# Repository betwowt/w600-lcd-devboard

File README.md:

# W600 LCD DevBoard

**用两块钱的 W600 模组和一块 ILI9341 240×320 屏，做出一块能点屏、能触摸、能读卡、能存图的开源板。**
硬件（KiCad / Gerber / BOM / 3D）、固件、构建脚本和实测记录都在这个仓库里。

## 为什么做这块板

W600 是 WinnerMicro 2019 年的模组，逛某宝时两元一片，卖家说兼容 ESP8266。
买回来实测发现：模块自带的 AT 固件是裁剪版，没有 HTTP / MQTT 专用 AT、
server 模式和 OTA，多轮 socket 开关后状态机还会残留（详见
[`docs/W600-AT-baseline.md`](docs/W600-AT-baseline.md)）。

既然 AT 不够用，就基于 W600 SDK 自己写固件。于是有了这块板：把点屏要用的
FPC、触摸、外部 Flash、TF 卡，以及按键、RGB 灯和 USB-C 串口都做上，
顺手把 LCD / Flash / SD 三设备共享 SPI 的坑也踩完了。

## 特性

- **显示**：ILI9341 240×320 SPI，20 MHz 硬件 SPI 刷屏，1bpp 图像快速展开
- **触摸**：FT6236 / CST816 自动探测，I2C 轮询，支持画板演示
- **存储**：板载 W25Q64（8 MB）+ TF 卡，FAT16/32 文件流
- **开机 logo**：TF 卡 `/logo.bin` 同步到 Flash，之后从 Flash 流式刷屏
- **Bad Apple**：TF 卡实时播放 1bpp 帧流，RLE 压缩，240×180 实测 18 fps
- **交互**：4 个用户按键 + 共阳 RGB 灯，全部挂在 XL9555 上
- **自检**：一块固件检查 LCD、Flash、TF 卡和 Wi-Fi，失败时串口打印具体阶段
- **共享总线**：LCD / Flash / SD 共用 SPI，单总线任务 + CS 互锁，不会互相踩
- **全开源**：原理图、PCB、Gerber、BOM、LCSC 库、3D 模型和固件源码都在仓库里

## 硬件

| 项目 | 规格 |
| --- | --- |
| MCU | WinnerMicro W600（TW-03），Cortex-M3 @ 80 MHz，2.4 GHz 802.11 b/g/n |
| 存储 | 1 MB Flash / 288 KB SRAM |
| 模组封装 | ESP-12F 兼容封装 |
| 屏幕 | ILI9341 240×320，16Pin 0.5 mm FPC，SPI，无 MISO |
| 触摸 | FT6236 / CST816，I2C，TP_INT 可选 |
| 外部 Flash | W25Q64，8 MB，SPI NOR |
| 存储卡 | TF 卡槽，SPI 模式，FAT16/32 |
| IO 扩展 | XL9555，16 位 I2C GPIO，地址 `0x24` |
| USB | USB-C 供电 + CH340N USB-UART |
| 电源 | AMS1117-3.3，USB-C 5 V 输入 |
| 按键 | 4 个用户键（KEY0–KEY3）+ 1 个复位键 |
| 指示灯 | XL-1615RGBC-RF 共阳 RGB，低有效 |
| PCB | 2 层，1.6 mm，约 45.8 × 34.6 mm |

```mermaid
flowchart LR
  PC[USB-C 5V] --> LDO[AMS1117-3.3]
  USB[USB-C D+/D-] --> CH[CH340N]
  CH -->|UART| W[W600]
  W -->|SPI PA01/PB18/PB17| BUS{共享 SPI 总线}
  BUS --> LCD[ILI9341 240x320]
  BUS --> FL[W25Q64 8MB]
  BUS --> TF[TF 卡]
  W -->|I2C PB09/PB12| X[XL9555]
  X --> LCD
  X --> KEY[4 按键]
  X --> RGB[RGB LED]
  W -->|I2C PB13/PB14| TP[FT6236/CST816]
```

### 引脚分配

| 信号 | W600 / 扩展 | 说明 |
| --- | --- | --- |
| SPI_CLK | PA01 | LCD / Flash / SD 共用，AF option 3 |
| SPI_MOSI | PB18 | 共用，AF option 3 |
| SPI_MISO | PB17 | Flash / SD 共用；LCD 不接 MISO |
| LCD_CS | PB11 | GPIO 片选，低有效 |
| LCD_DC | XL9555 P0_3 | 命令/数据 |
| LCD_RST | XL9555 P0_0 | 低有效 |
| LCD_PWR | XL9555 P0_2 | 高有效（面板使能/背光电源） |
| FLASH_CS | PB15 | W25Q64 片选，低有效 |
| SD_CS | PB16 | TF 卡片选，低有效 |
| XL9555_SCL | PB09 | 软件 I2C（该脚无硬件 I2C 复用） |
| XL9555_SDA | PB12 | 软件 I2C，4.7 kΩ 上拉 |
| XL9555_INT | PB08 | 本仓库未使用 |
| TOUCH_SCL | PB13 | 触摸 I2C，4.7 kΩ 上拉 |
| TOUCH_SDA | PB14 | 触摸 I2C，4.7 kΩ 上拉 |
| TP_RST | XL9555 P0_1 | 触摸复位，低有效 |
| TP_INT | PB10 | 触摸中断，本例程轮询 |
| KEY0–KEY3 | XL9555 P0_4–P0_7 | 10 kΩ 上拉，按下为低 |
| LED_R/G/B | XL9555 P1_0–P1_2 | 共阳 +3.3 V，低有效 |

注意：`PB11/PB12` 被 LCD_CS 和 XL9555 占用，SDK 默认 UART1 不能同时使用。

### 关键器件

| 器件 | 型号 | 封装 / LCSC |
| --- | --- | --- |
| 主控模组 | W600 / TW-03 | ESP-12F 兼容，LCSC `C19949064` 封装 |
| USB-UART | CH340N | SOP-8，`C2977777` |
| 3.3 V LDO | AMS1117-3.3 | SOT-223，`C6186` |
| SPI NOR | W25Q64（8 MB） | SOP-8，`C2985658` |
| IO 扩展 | XL9555 | TSSOP-24，`C609791` |
| LCD 座 | 16P 0.5 mm FPC | `C2856801` |
| TF 卡座 | push-push | `C393941` |
| RGB 灯 | XL-1615RGBC-RF | `C965840` |
| 按键 | SMD tact | `C720477` |

> BOM 里 U1 标的是 `W25Q64JWSSIQ`（1.8 V 型号），但板上 VCC/WP/HOLD 都接
> `+3.3 V`。实装请以丝印为准；若用 3.3 V 型号（`W25Q64JV/FV`）可直接忽略
> 这条 BOM 记录。

原理图、PCB、Gerber、交互式 BOM 和 3D 模型都在
`hardware/W600模组开发板/`，用 KiCad 打开 `W600模组开发板.kicad_pro`。

## 快速开始

### 1. 烧录固件

不编译也能先跑：`software/prebuilt/` 下有三个已验证镜像。

| 镜像 | MD5 | 用途 |
| --- | --- | --- |
| `software/prebuilt/normal/lcd.fls` | `1791c60b82ef57f549977b33b2b58be5` | 点屏 + Flash logo + 触摸演示 |
| `software/prebuilt/board/lcd.fls` | `40599329128e30d0ccb35f0766beda27` | 整板自检；会擦除 W25Q64 最后一个 4 KB 扇区 |
| `software/prebuilt/badapple/lcd.fls` | `37d9c99c9a29b558624ee2ace29a5a39` | 播放 TF 卡 `/BADAPPLE.BIN` |

W600 要进 secboot，得在上电或复位时拉低 boot 脚；串口出现 `CCC...` 后才能烧录。
板上 CH340N 没有 DTR/RTS，**不能自动复位进下载模式**，需要手动操作；
烧录前先关掉串口助手，避免 COM 口被独占。

```bash
# 在 W600 SDK 的 example 目录，产物为 bin/lcd/lcd.fls
make -f Makefile.mk APP_BIN_NAME=lcd TARGET=lcd COMPILE=gcc FLASH_SIZE=1M \
     DL_PORT=COM10 DL_BAUD=921600 flash
```

也可以直接用 `w600tool` 写 `lcd.fls`。镜像 MD5 会随编译时间变化
（`__DATE__` / `__TIME__`），以构建脚本输出为准。

### 2. 编译

依赖 W600 SDK 3.4.0、`arm-none-eabi-gcc` 7-2017q4 和 GNU make。

```powershell
# 普通点屏 / Flash logo / 触摸
pwsh -File software/build-lcd.ps1 -Variant normal

# 整板自检
pwsh -File software/build-lcd.ps1 -Variant board

# 只探测外部 Flash
pwsh -File software/build-lcd.ps1 -Variant flashonly

# TF 卡 Bad Apple 播放
pwsh -File software/build-lcd.ps1 -Variant badapple
```

脚本默认找 `F:/projects/w600-sdk`，也可以设 `W600_SDK` 环境变量或传
`-SdkRoot`；工具链默认从 Arduino15 路径查找，可用 `-Toolchain` 覆盖。
流程是：复制 `software/lcd` 到 `$SdkRoot/example/lcd` → 调 SDK 的
`example/Makefile.mk` → 生成 `bin/lcd/lcd.fls` → 复制到
`software/prebuilt/<variant>/`。

### 3. 准备 TF 卡

FAT32、MBR 分区，文件名用 8.3 格式：

```text
/logo.bin       开机图片（可选）
/BADAPPLE.BIN   Bad Apple 帧流（badapple 变体）
```

`/logo.bin` 是 20 字节头 + RGB565 大端像素：

```text
"LOGO" | u16 w | u16 h | u16 fmt=1 | u16 reserved | u32 data_size | u32 reserved
```

有卡时固件会比较 TF 卡和 Flash 里的内容，不同才擦写，避免反复磨损；没有卡或
没有文件就直接用 Flash 里已有的 logo。

### 4. 首次上电

1. 插好 16Pin FPC，USB-C 供电，串口按 **115200 8N1** 打开
2. 启动日志会打印 XL9555 探测、Flash JEDEC ID、SD 初始化和 logo 同步结果
3. 开机先显示 logo 3 秒，然后进入彩条 + 触摸画板演示
4. `badapple` 变体在 logo 后循环播放，按任意用户键停止并进入触摸演示

## 固件变体

| 变体 | 编译开关 | 行为 |
| --- | --- | --- |
| `normal` | — | 点屏、Flash logo、触摸画板 |
| `board` | `-DBOARD_CHECK -DSD_DIAG` | LCD / Flash / TF / Wi-Fi 自检，结果上屏 + 串口日志 |
| `flashonly` | `-DFLASH_ONLY` | 只探测并打印 W25Q64 ID |
| `badapple` | `-DBAD_APPLE` | 播放 TF 卡 `/BADAPPLE.BIN` |
| `overclock` | `-DOC_TEST` | 80/40/80/160 MHz 负载对比，160 MHz 会挂死 |

`overclock` 镜像不预置，需要本地构建。实测 40 MHz 下各项耗时约为 80 MHz 的
2.0 倍，80 MHz 重跑误差 <0.3%；160 MHz 切换后串口无输出、板子挂死，
按复位键并重刷 `normal` 即可恢复。W600 标称 80 MHz，没有可用的中间档位。

## 功能与实测

### 点屏与触摸

`lcd.c` 负责 ILI9341 初始化、填充、画线/矩形、8×16 字体和 1bpp 图像流；
`lcd_demo.c` 复刻 STM32 参考工程的彩条、灰阶和触摸画板。触摸初始化会把
`TP_RST` 拉低 10 ms、释放 120 ms，再探测 `0x38`（FT6236）或 `0x15`
（CST816）。

### Flash logo

`w25qxx.c` 管理 W25Q64：ID 和短命令走 GPIO bit-bang，长块读写优先
20 MHz 主机 SPI DMA，失败自动回退。logo 固定放在 `0x700000`，占 256 KB；
`0x7FF000` 留给板级自检擦写，不会碰固件区。

这块板的 W600 主机 SPI 读 Flash 在所有模式下都返回 `FF`，所以 ID 和
状态寄存器必须走 bit-bang；LCD 仍然用主机 SPI。每次切换后由
`lcd_spi_resume()` 把总线恢复成 Mode 0。

### Bad Apple

`tools/bad_apple.py` 用 ffmpeg 解码，按硬阈值或 Bayer 抖动压成 1bpp，
默认输出 RLE 帧流。推荐先按下面三档生成（BIN 体积大，不随仓库提交）：

| 文件 | 分辨率 | fps | 格式 | 大小 |
| --- | --- | --- | --- | --- |
| `BADAPPLE.BIN` | 240×180 | 18 | RLE | 2.33 MB |
| `BADAPPLE_FAST.BIN` | 192×144 | 24 | RLE | 2.34 MB |
| `BADAPPLE_TINY.BIN` | 160×120 | 24 | RLE | 1.82 MB |
| `BADAPPLE_RAW_240X180_12FPS.BIN` | 240×180 | 12 | raw | 14 MB |

复制要播的文件到 TF 卡并改名 `BADAPPLE.BIN`。RLE 把 240×180 的 SD 流量
从 5400 B/帧压到约 620 B/帧；LCD 数据固定 86.4 KB，20 MHz 下约 35 ms，
所以 18 fps 的瓶颈在 LCD，不在卡。完整帧格式和刷屏路径见
[`software/lcd/README.md`](software/lcd/README.md)。

### 整板自检

`board` 变体依次验证 LCD、W25Q64、TF 卡和 Wi-Fi 扫描，屏幕显示三行
PASS/FAIL，串口打印细节。失败项会给出具体阶段，例如
`LCD init failed`、`FLASH: 0x9F BB ...`、`SD: CMD0 try ...`。

## 软件结构

```text
software/lcd/user/
  main.c          启动流程和任务入口
  lcd.c            ILI9341 驱动
  lcd_demo.c       彩条 / 画板演示
  touch.c          FT6236 / CST816
  xl9555.c         LCD 电源/复位/DC/按键/RGB
  spi_bus.c        LCD / Flash / SD 共享总线，队列 + CS 互锁
  w25qxx.c         W25Q64 驱动
  sd_fs.c          SD 卡 bit-bang + FAT16/32
  logo.c           TF → Flash logo 同步与显示
  badapple.c       TF 流式播放
  ba_rle.c         LEB128 RLE 解码（纯 C，可主机测试）
  board_check.c    整板自检
  drivers_test.c   按键 / RGB 自测
  oc_test.c        超频对比
```

三个 SPI 设备共用 `PA01/PB18/PB17`，`spi_bus.c` 用一个总线任务串行化
事务：调用者投递后阻塞，只有总线任务能改 CS 和时序；`g_cs_low_dev`
保证同一时刻最多一个片选为低，事务结束强制恢复主机 SPI 复用，
避免 SD/Flash bit-bang 之后 LCD 花屏。

## 目录

```text
hardware/                 KiCad 工程、Gerber、iBOM、LCSC/3D 模型
software/lcd/             W600 SDK 应用源码
software/build-lcd.ps1    复制源码进 SDK 并编译
software/prebuilt/        已验证的预编译镜像
scripts/                  W600 AT 模块的串口 / 性能 / 长跑脚本
tools/                    Bad Apple 转换、ESP-AT 下载脚本
partitions/               ESP32-C3 2MB AT 分区表
docs/W600-AT-baseline.md  W600 AT 固件实测、速率与稳定性记录
docs/images/board.jpg     实物图
```

`firmware/`、`build/`、`results/`、`.tmp/` 和 `logo.bin` 是本地素材/输出，
不进入仓库。

## W600 AT 模块实测

`docs/W600-AT-baseline.md` 记录了同一批 TW-03 的完整基线，结论先放这里：

| 能力 | 结果 |
| --- | --- |
| TCP client / UDP / DNS / PING | ✅ |
| TLS | ✅ 模块内完成 |
| TCP server / 多路 socket | ❌ |
| HTTP / MQTT 专用 AT | ⚠️ 没有，需 TCP/SSL 手写 |
| 921600 UART 下 TCP↓ | 83.9 KB/s（0.67 Mbps，93% UART） |
| UDP↑ | 32 KB/s（单次 ≤2048 B） |
| 10 小时长跑 | 3621 轮，MQTT 回环 99.97%，HTTP 120/120 |

**瓶颈是 921600 UART，不是 Wi-Fi。** 要更高吞吐只能用 W600 SDK 自己写
TCP/UDP，或者换 ESP32。AT 固件没有源码，也没有 secboot 通道；socket
状态机残留只能靠主机侧重连规避。

## 常见问题

**屏全黑，但串口有初始化日志？**
先量 FPC 11 脚 `LCD_PWR` 是否为高；若面板使能低有效，把
`xl9555_init()` 里的 `XL9555_P0_LCD_PWR` 取反。再确认 XL9555 地址
`0x24` 和 PB09/PB12 上拉。

**花屏 / 闪烁？**
把 `LCD_SPI_HZ` 从 20 MHz 降到 10 MHz。

**红蓝反了 / 方向不对？**
红蓝反改 ILI9341 `0x36` 参数（`0x08` → `0x00`）；方向不对按参考工程
改 `0xC8/0x78/0xA8` 并同步交换宽高。

**触摸没反应？**
确认 `TP_RST` 已释放、I2C 上拉正常，并看启动日志探测到 `0x38` 还是
`0x15`；两种芯片坐标寄存器相同。

**Flash ID 读到 `FF FF FF`？**
核对 U1 丝印和供电（BOM 的 1.8 V 型号 vs 板上 3.3 V）、PB15 片选、
PB17 MISO。固件探测前会先发 `0xFF/0xAB/0x66+0x99` 退出 QPI、释放
掉电和软复位。

**TF 卡不识别 / 掉帧？**
用 FAT32 + MBR，文件名 8.3；看启动日志的 `SD: data clock ...`。
固件会从 8 MHz 逐档降到 400 kHz，卡慢时会自动降档。

**烧录进不去 secboot？**
先关串口助手；手动拉低 boot 脚再复位/上电，看到 `CCC...` 再写。
CH340N 没有 DTR/RTS，不能靠工具自动复位。

**为什么 Flash/SD 用 GPIO bit-bang，不用硬件 SPI？**
这块板的 W600 主机 SPI 读 Flash 和 SD 的 R1 都会错位（CMD0 返回
`0xC0`），硬件 mode 0/3 都不行；同一张卡 bit-bang 正常。主机 SPI 留给
LCD，Flash/SD 的 bit-bang 时序由 `spi_bus` 统一调度。

## 验证状态

| 项目 | 状态 |
| --- | --- |
| LCD 初始化 / 刷屏 / 文字 / 图形 | ✅ 板上验证 |
| 触摸 FT6236 / CST816 | ✅ 板上验证 |
| W25Q64 ID / 读 / 写 / 擦除 | ✅ 板上验证 |
| TF 卡 FAT16/32 + logo 同步 | ✅ 板上验证 |
| Bad Apple RLE 播放 | ✅ 240×180 @ 18 fps |
| 4 按键 + RGB | ✅ 驱动自测 |
| 整板自检 | ✅ |
| Wi-Fi 应用 | ⚠️ 未集成到本仓库固件，AT 实测见 docs |
| 160 MHz 超频 | ❌ 挂死，无可用档位 |

## 资料与交流

- W600 SDK 3.4.0（官方）+ `arm-none-eabi-gcc` 7-2017q4
- 器件数据手册随 LCSC 库放在 `hardware/.../easyeda_convertlib.datasheet/`
- W600 的公开资料比较零散，仓库里整理了一部分，放在 `docs/`；其余 SDK、
  AT 固件和手册在交流群文件里
- 有问题欢迎开 Issue，带上串口日志和板上丝印/版本

## 说明

- W600 是清库存模组，**没有长期供货和固件维护承诺**，量产前先确认 BOM
  和 secboot 烧录工装（boot 脚必须能拉低）。
- 本仓库的 AT 实测只针对手上这批 TW-03，不同批次/固件的命令集可能不同。
- 硬件按 3.3 V 设计；换 1.8 V Flash 型号时必须同时改供电，不能只改 BOM。

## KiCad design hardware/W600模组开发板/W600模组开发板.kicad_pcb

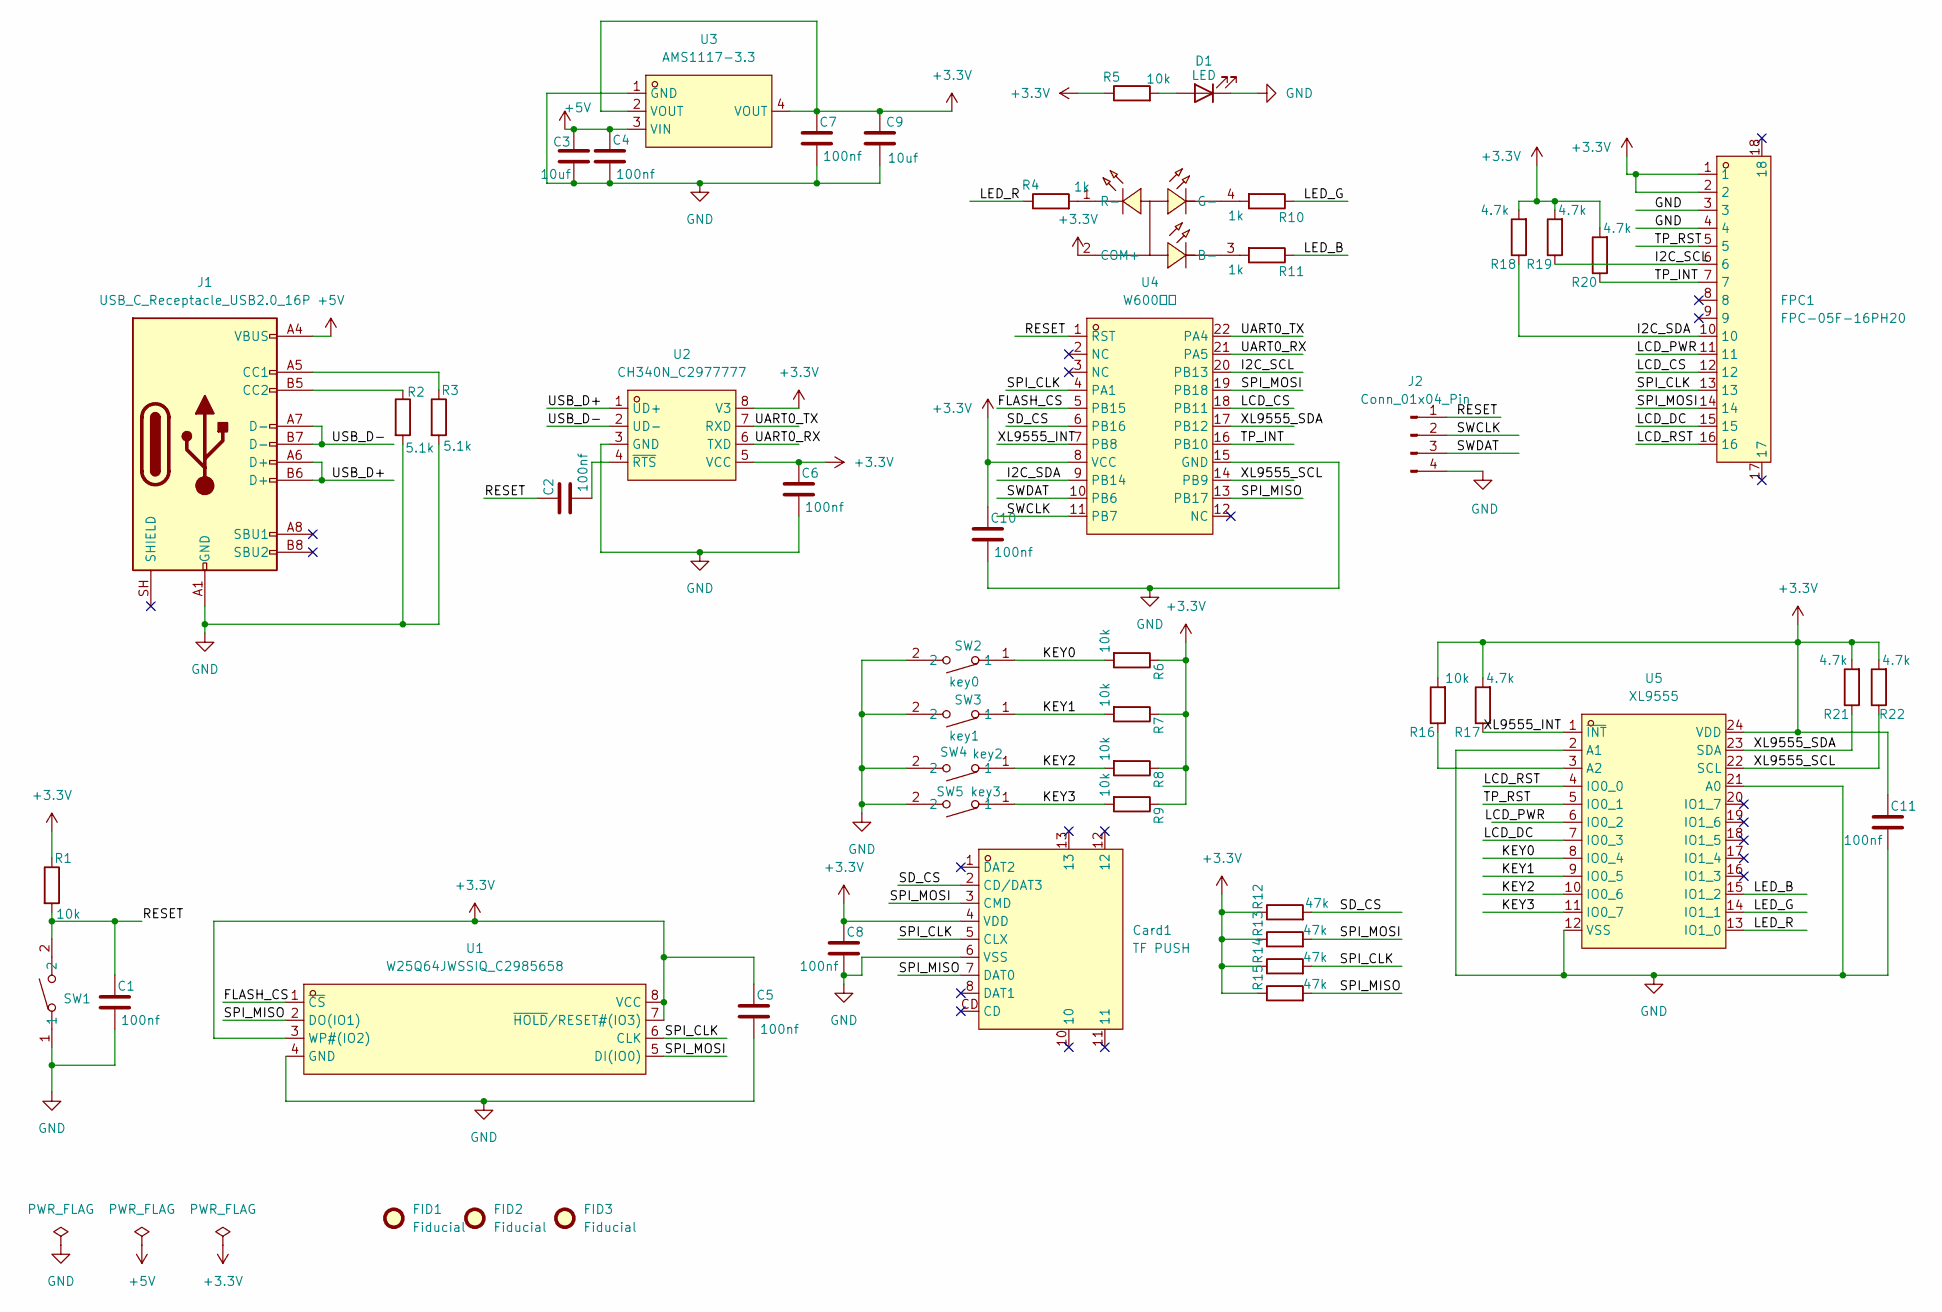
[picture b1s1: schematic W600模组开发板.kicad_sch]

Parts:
C1, C2, C4, C5, C6, C7, C8, C10, C11: 100nf; C_0603_1608Metric
C3, C9: 10uf; C_0805_2012Metric
Card1: TF PUSH; C393941_TF-SMD_TF-PUSH; MPN TF PUSH; LCSC Part C393941
D1: LED; LED_0603_1608Metric
FID1, FID2, FID3: Fiducial; Fiducial_0.5mm_Mask1mm
FPC1: FPC-05F-16PH20; C2856801_FPC-SMD_16P-P0.50_FPC-05F-16PH20; MPN FPC-05F-16PH20; LCSC Part C2856801
J1: USB_C_Receptacle_USB2.0_16P; USB_C_Receptacle_GCT_USB4105-xx-A_16P_TopMnt_Horizontal
J2: Conn_01x04_Pin; PinHeader_1x04_P2.54mm_Vertical
LED1: XL-1615RGBC-RF; C965840_LED-ARRAY-SMD_4P-L1.6-W1.5-BR_XL-1615RGBC-RF; MPN XL-1615RGBC-RF; LCSC Part C965840
R1, R5, R6, R7, R8, R9, R16: 10k; R_0603_1608Metric
R2, R3: 5.1k; R_0603_1608Metric
R4, R10, R11: 1k; R_0603_1608Metric
R12, R13, R14, R15: 47k; R_0603_1608Metric
R17, R18, R19, R20, R21, R22: 4.7k; R_0603_1608Metric
SW1: reset; C720477_SW-SMD_L3.9-W3.0-P4.45; MPN TS-1088-AR02016; LCSC Part C720477
SW2: key0; C720477_SW-SMD_L3.9-W3.0-P4.45; MPN TS-1088-AR02016; LCSC Part C720477
SW3: key1; C720477_SW-SMD_L3.9-W3.0-P4.45; MPN TS-1088-AR02016; LCSC Part C720477
SW4: key2; C720477_SW-SMD_L3.9-W3.0-P4.45; MPN TS-1088-AR02016; LCSC Part C720477
SW5: key3; C720477_SW-SMD_L3.9-W3.0-P4.45; MPN TS-1088-AR02016; LCSC Part C720477
U1: W25Q64JWSSIQ_C2985658; C2985658_SOP-8_L5.3-W5.2-P1.27-LS7.9-BL; MPN W25Q64JWSSIQ; LCSC Part C2985658
U2: CH340N_C2977777; C2977777_SOP-8_L4.9-W3.9-P1.27-LS6.0-BL; MPN CH340N; LCSC Part C2977777
U3: AMS1117-3.3; C6186_SOT-223-3_L6.5-W3.4-P2.30-LS7.0-BR; MPN AMS1117-3.3; LCSC Part C6186
U4: W600模组; C19949064_WIRELM-SMD_ESP-12F; MPN ESP-12F; LCSC Part C19949064
U5: XL9555; C609791_TSSOP-24_L7.8-W4.4-P0.65-LS6.4-BL; MPN XL9555; LCSC Part C609791

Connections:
+3.3V: C5.1, C6.1, C7.1, C8.1, C9.1, C10.1, C11.1, Card1.4 (VDD), FPC1.1, FPC1.2, LED1.2 (COM+), R1.1, R5.1, R6.1, R7.1, R8.1, R9.1, R12.1, R13.1, R14.1, R15.1, R16.2, R17.2, R18.2, R19.2, R20.2, R21.2, R22.2, U1.3 (WP#(IO2)), U1.7 (~HOLD/RESET#(IO3)), U1.8 (VCC), U2.5 (VCC), U2.8 (V3), U3.2 (VOUT), U3.4 (VOUT), U4.8 (VCC), U5.24 (VDD)
+5V: C3.1, C4.1, J1.A4 (VBUS), J1.A9 (VBUS), J1.B4 (VBUS), J1.B9 (VBUS), U3.3 (VIN)
/FLASH_CS: U1.1 (~CS), U4.5 (PB15)
/I2C_SCL: FPC1.6, R19.1, U4.20 (PB13)
/I2C_SDA: FPC1.10, R18.1, U4.9 (PB14)
/KEY0: R6.2, SW2.1, U5.8 (IO0_4)
/KEY1: R7.2, SW3.1, U5.9 (IO0_5)
/KEY2: R8.2, SW4.1, U5.10 (IO0_6)
/KEY3: R9.2, SW5.1, U5.11 (IO0_7)
/LCD_CS: FPC1.12, U4.18 (PB11)
/LCD_DC: FPC1.15, U5.7 (IO0_3)
/LCD_PWR: FPC1.11, U5.6 (IO0_2)
/LCD_RST: FPC1.16, U5.4 (IO0_0)
/LED_B: R11.1, U5.15 (IO1_2)
/LED_G: R10.1, U5.14 (IO1_1)
/LED_R: R4.1, U5.13 (IO1_0)
/RESET: C1.1, C2.1, J2.1, R1.2, SW1.2, U4.1 (RST)
/SD_CS: Card1.2 (CD/DAT3), R12.2, U4.6 (PB16)
/SPI_CLK: Card1.5 (CLX), FPC1.13, R14.2, U1.6 (CLK), U4.4 (PA1)
/SPI_MISO: Card1.7 (DAT0), R15.2, U1.2 (DO(IO1)), U4.13 (PB17)
/SPI_MOSI: Card1.3 (CMD), FPC1.14, R13.2, U1.5 (DI(IO0)), U4.19 (PB18)
/SWCLK: J2.2, U4.11 (PB7)
/SWDAT: J2.3, U4.10 (PB6)
/TP_INT: FPC1.7, R20.1, U4.16 (PB10)
/TP_RST: FPC1.5, U5.5 (IO0_1)
/UART0_RX: U2.6 (TXD), U4.21 (PA5)
/UART0_TX: U2.7 (RXD), U4.22 (PA4)
/USB_D+: J1.A6 (D+), J1.B6 (D+), U2.1 (UD+)
/USB_D-: J1.A7 (D-), J1.B7 (D-), U2.2 (UD-)
/XL9555_INT: R17.1, U4.7 (PB8), U5.1 (~INT)
/XL9555_SCL: R22.1, U4.14 (PB9), U5.22 (SCL)
/XL9555_SDA: R21.1, U4.17 (PB12), U5.23 (SDA)
GND: C1.2, C3.2, C4.2, C5.2, C6.2, C7.2, C8.2, C9.2, C10.2, C11.2, Card1.6 (VSS), D1.1 (K), FPC1.3, FPC1.4, J1.A1 (GND), J1.A12 (GND), J1.B1 (GND), J1.B12 (GND), J2.4, R2.2, R3.2, SW1.1, SW2.2, SW3.2, SW4.2, SW5.2, U1.4 (GND), U2.3 (GND), U3.1 (GND), U4.15 (GND), U5.2 (A1), U5.12 (VSS), U5.21 (A0)
unnamed: D1.2 (A), R5.2
unnamed: J1.A5 (CC1), R3.1
unnamed: J1.B5 (CC2), R2.1
unnamed: LED1.3 (B-), R11.2
unnamed: LED1.4 (G-), R10.2
unnamed: LED1.1 (R-), R4.2
unnamed: C2.2, U2.4 (~RTS)
unnamed: R16.1, U5.3 (A2)

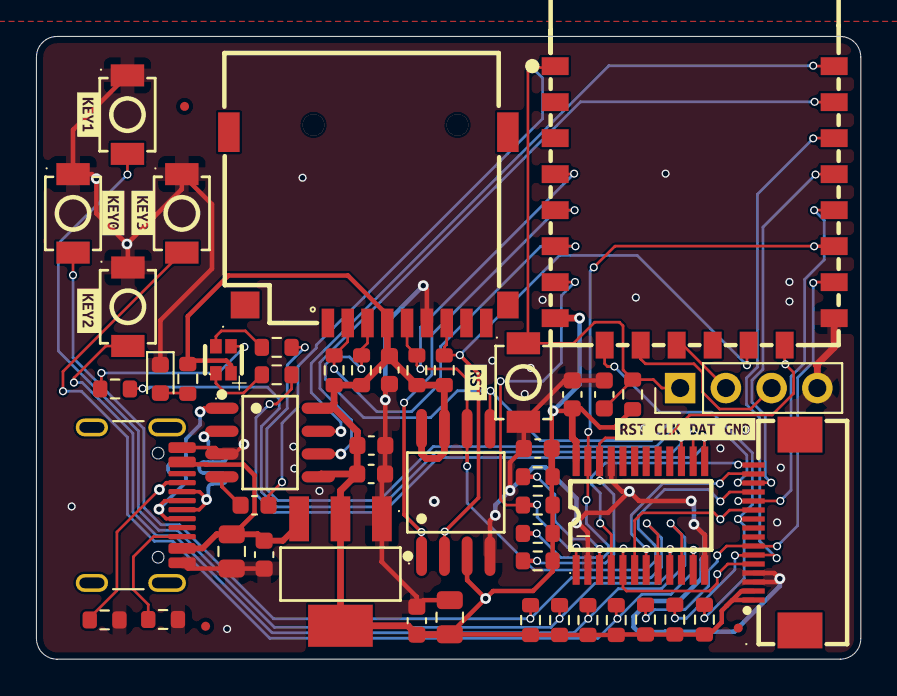
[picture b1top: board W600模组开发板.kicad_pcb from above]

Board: 2 copper layers, 45.8 x 34.6 mm, 58 parts (0 on the bottom side), 41 nets.

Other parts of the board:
kibuzzard-6AFE51E4: G***; kibuzzard-6AFE51E4
kibuzzard-6AFE516F: G***; kibuzzard-6AFE516F
kibuzzard-6AFE520B: G***; kibuzzard-6AFE520B
kibuzzard-6AFE5150: G***; kibuzzard-6AFE5150
kibuzzard-6AFE5163: G***; kibuzzard-6AFE5163
kibuzzard-6AFE5176: G***; kibuzzard-6AFE5176

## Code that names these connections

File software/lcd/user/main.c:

/*
 * W600 module dev board LCD demo.
 *
 * Panel: ILI9341 240x320 SPI, 16-pin FPC
 *   SPI_CLK  PA01        LCD_CS   PB11
 *   SPI_MOSI PB18        LCD_DC   XL9555 P0_3
 *   LCD_RST  XL9555 P0_0 LCD_PWR  XL9555 P0_2
 *   XL9555 SCL PB09 / SDA PB12, address 0x24
 *   Touch: I2C PB13/PB14, TP_RST XL9555 P0_1, TP_INT PB10 (polling)
 *
 * The drawing state matches the STM32 P024C135 demo: text, full-screen
 * colors, color bars, grayscale, then handwriting with a white brush and a
 * Clear button in the bottom-right corner.
 */
#include "board.h"
#include "lcd.h"
#include "logo.h"
#include "touch.h"
#include "xl9555.h"
#include "lcd_demo.h"
#include "drivers_test.h"
#include "spi_bus.h"
#include "w25qxx.h"
#ifdef BAD_APPLE
#include "badapple.h"
#endif
#ifdef BOARD_CHECK
#include "board_check.h"
#endif

#if defined(BOARD_CHECK) && (defined(LCD_TEST) || defined(DRIVER_TEST))
#error "BOARD_CHECK is exclusive with LCD_TEST and DRIVER_TEST"
#endif


/*
 * The prebuilt SDK libs (libapp.a) were compiled against newlib 2.1, which
 * used __ctype_ptr__. Newer newlib only exports _ctype_, so provide the
 * pointer the old HTTP string helpers reference.
 */
extern const char _ctype_[];
const char *__ctype_ptr__ = &_ctype_[1];

/*
 * 8 KB stack: the SD/FAT path was reliable at this size. Do not shrink it
 * for the half-frame logo buffer; the W600 RAM region still fits.
 */
#define USER_TASK_STK_SIZE  2048
#define USER_TASK_PRIO      32

static u32 user_task_stk[USER_TASK_STK_SIZE];

#ifdef LCD_TEST
static void lcd_test_loop(void)
{
    printf("LCDTEST: start (re-init after each PWR change)\r\n");

    for (;;) {
        if (lcd_init_pwr(0) == 0) {
            lcd_fill(0, 0, LCD_W - 1, LCD_H - 1, LCD_RED);
            lcd_text(20, 140, "PWR LOW", LCD_WHITE, LCD_RED, 2);
            printf("LCDTEST: PWR low, red\r\n");
        } else {
            printf("LCDTEST: PWR low init failed\r\n");
        }
        DELAY_MS(3000);

        if (lcd_init_pwr(1) == 0) {
            lcd_fill(0, 0, LCD_W - 1, LCD_H - 1, LCD_GREEN);
            lcd_text(20, 140, "PWR HIGH", LCD_WHITE, LCD_GREEN, 2);
            printf("LCDTEST: PWR high, green\r\n");
        } else {
            printf("LCDTEST: PWR high init failed\r\n");
        }
        DELAY_MS(3000);
    }
}
#endif

static void lcd_demo_task(void *arg)
{
    int ret;
    int has_logo = 0;

    (void)arg;

#ifdef FLASH_ONLY
    for (;;) {
        printf("FLASHONLY: probe\r\n");
        (void)w25qxx_init();
        DELAY_MS(2000);
    }
#endif

    ret = lcd_init();
    if (ret != 0) {
        printf("LCD init failed: %d (check XL9555 on PB9/PB12, 0x24)\r\n", ret);
#ifdef BOARD_CHECK
        printf("BOARD: continuing UART tests without LCD\r\n");
#else
        for (;;) {
            DELAY_MS(1000);
            printf("LCD init failed: %d\r\n", ret);
            xl9555_diag();
        }
#endif
    }

#if !defined(LCD_TEST) && !defined(DRIVER_TEST) && !defined(BOARD_CHECK)
    /*
     * SD init must come after lcd_init(): the earlier working sequence
     * had XL9555/LCD_PWR and the shared pins already settled.
     */
    has_logo = (lcd_logo_load() == 0);
#endif

#ifdef LCD_TEST
    lcd_test_loop();
#endif

#ifdef DRIVER_TEST
    drivers_test();
#endif

#ifdef BOARD_CHECK
    board_check_run();
#endif

#if !defined(LCD_TEST) && !defined(DRIVER_TEST) && !defined(BOARD_CHECK)
    if (has_logo)
        lcd_logo_display();
    DELAY_MS(3000);
#endif

#ifdef BAD_APPLE
    /* Streams /BADAPPLE.BIN until a key is pressed, then falls through. */
    (void)badapple_run();
#endif

#if !defined(LCD_TEST) && !defined(DRIVER_TEST) && !defined(BOARD_CHECK)
    if (touch_init() != 0)
        printf("TOUCH: demo continues without touch\r\n");

    lcd_demo_run();
#endif
}

void pre_gpio_config(void)
{
    /*
     * Called from wm_gpio_config() before the SPI/flash drivers start.
     * Keep both chip selects deasserted while the bus is still floating.
     */
    tls_gpio_cfg(WM_IO_PB_11, WM_GPIO_DIR_OUTPUT, WM_GPIO_ATTR_FLOATING);
    tls_gpio_write(WM_IO_PB_11, 1);   /* LCD_CS */
    tls_gpio_cfg(WM_IO_PB_15, WM_GPIO_DIR_OUTPUT, WM_GPIO_ATTR_PULLHIGH);
    tls_gpio_write(WM_IO_PB_15, 1);   /* W25Q64 CS */

    /*
     * PB15 is the W600 default hspi_cs.  Move the hardware CS mux to the
     * unexposed PB00 so the host SPI controller cannot drive PB15 while
     * the LCD is using the shared CLK/MOSI lines.
     */
    wm_spi_cs_config(WM_IO_PB_00);

    /*
     * SD_CS must be high while the card powers up, otherwise it can enter
     * native SD mode instead of SPI mode (observed as CMD0 -> 00).
     */
    tls_gpio_cfg(WM_IO_PB_16, WM_GPIO_DIR_OUTPUT, WM_GPIO_ATTR_PULLHIGH);
    tls_gpio_write(WM_IO_PB_16, 1);   /* SD_CS */
}

void UserMain(void)
{
    printf("\r\nW600 LCD demo, compile @%s %s\r\n", __DATE__, __TIME__);
    printf("Panel ILI9341 240x320; SPI PA1/PB18, CS PB11, ctrl XL9555@0x24\r\n");

    spi_bus_init();

    tls_os_task_create(NULL,
            "lcd",
            lcd_demo_task,
            (void *)0,
            (void *)user_task_stk,
            USER_TASK_STK_SIZE * sizeof(u32),
            USER_TASK_PRIO,
            0);

    /*
     * Keep the startup task here instead of returning into
     * tls_sys_auto_mode_run(): the demo never touches SPI flash while the
     * LCD owns the shared SPI bus.
     */
    for (;;)
        tls_os_time_delay(0x10000000);
}

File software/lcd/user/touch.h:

/*
 * Touch controller on the LCD FPC.
 *
 * TP_RST  = XL9555 P0_1
 * TP_INT  = PB10 (not used, polling)
 * I2C_SCL = PB13, I2C_SDA = PB14
 */
#ifndef TOUCH_H
#define TOUCH_H

#include "board.h"

int touch_init(void);
/* 0 = no touch, 1 = touched, -1 = I2C error */
int touch_read(u16 *x, u16 *y);

#endif /* TOUCH_H */

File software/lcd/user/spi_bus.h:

/*
 * Shared SPI bus: one command queue, one device owning the bus at a time.
 *
 * Devices on PA01/PB18/PB17:
 *   LCD   CS PB11   (hardware SPI, 20 MHz)
 *   Flash CS PB15   (GPIO bit-bang)
 *   TF    CS PB16   (GPIO bit-bang)
 *
 * Drivers submit a transaction to the queue; a dedicated bus task executes
 * transactions in FIFO order.  Chip selects are driven only by
 * spi_bus_cs_low()/spi_bus_cs_high(), which enforce:
 *   - only the current transaction's device may drive its CS;
 *   - at most one CS may be low.
 * The worker force-deselects on every exit and restores the master-SPI mux,
 * so a bit-bang transaction can never leak into the next LCD transaction.
 */
#ifndef SPI_BUS_H
#define SPI_BUS_H

#include "board.h"

typedef enum {
    SPI_DEV_NONE = 0,
    SPI_DEV_LCD,
    SPI_DEV_FLASH,
    SPI_DEV_SD
} spi_dev_t;

void spi_bus_init(void);

/*
 * Submit fn(arg) to the bus queue and wait for it to finish.
 * fn runs in the bus task; it may call spi_bus_cs_low/high().
 * Returns fn's return value, or -1 if the queue is unavailable/full.
 */
int spi_bus_run(spi_dev_t dev, int (*fn)(void *arg), void *arg);

/* Called only from inside a queued transaction. */
int spi_bus_cs_low(spi_dev_t dev);
int spi_bus_cs_high(spi_dev_t dev);

/*
 * Per-device clock.  LCD reprograms the master SPI; Flash/SD select the
 * bit-bang half-period that meets their timing.  Must run in the device's
 * transaction (owner check).
 */
int spi_bus_set_clock(spi_dev_t dev, u32 hz);

/* Delay used by bit-bang drivers, derived from the current device clock. */
void spi_bus_bb_delay(void);

#endif /* SPI_BUS_H */

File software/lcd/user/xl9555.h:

/*
 * XL9555 16-bit I2C GPIO expander driver (software I2C).
 *
 * Board wiring (W600 module dev board):
 *   XL9555_SCL = PB09   (no hardware I2C SCL mux on this pin)
 *   XL9555_SDA = PB12
 *   XL9555_INT = PB08   (not used here)
 *   A2 = 1 (R16 to 3.3V), A1 = 0, A0 = 0  ->  7-bit address 0x24
 *
 * Port assignment:
 *   P0_0 LCD_RST   P0_1 TP_RST   P0_2 LCD_PWR   P0_3 LCD_DC
 *   P0_4..7 KEY0..KEY3 (inputs)
 *   P1_0..2 LED_R/G/B (active low)  P1_3..7 unused
 */
#ifndef XL9555_H
#define XL9555_H

#include "board.h"

#define XL9555_ADDR_DEFAULT 0x24

#define XL9555_P0_LCD_RST   (1u << 0)
#define XL9555_P0_TP_RST    (1u << 1)
#define XL9555_P0_LCD_PWR   (1u << 2)
#define XL9555_P0_LCD_DC    (1u << 3)
#define XL9555_P0_KEY0      (1u << 4)
#define XL9555_P0_KEY1      (1u << 5)
#define XL9555_P0_KEY2      (1u << 6)
#define XL9555_P0_KEY3      (1u << 7)

#define XL9555_P1_LED_R     (1u << 0)
#define XL9555_P1_LED_G     (1u << 1)
#define XL9555_P1_LED_B     (1u << 2)

/* Register map */
#define XL9555_REG_IN0      0x00
#define XL9555_REG_IN1      0x01
#define XL9555_REG_OUT0     0x02
#define XL9555_REG_OUT1     0x03
#define XL9555_REG_POL0     0x04
#define XL9555_REG_POL1     0x05
#define XL9555_REG_CFG0     0x06
#define XL9555_REG_CFG1     0x07

/* Configure pins, power the panel, assert reset. Returns 0 on success. */
int xl9555_init(void);
void xl9555_diag(void);

/* Reset the touch controller through P0_1 (10 ms low, 120 ms high). */
int xl9555_touch_reset(void);

/* Update output port 0/1 latches. Only changed bytes are written. */
int xl9555_p0_patch(u8 mask, u8 value);
int xl9555_p1_patch(u8 mask, u8 value);

int xl9555_write_regs(u8 reg, const u8 *buf, u8 len);
int xl9555_read_regs(u8 reg, u8 *buf, u8 len);

u8 xl9555_p0_value(void);
u8 xl9555_p1_value(void);
u8 xl9555_address(void);

#endif /* XL9555_H */
